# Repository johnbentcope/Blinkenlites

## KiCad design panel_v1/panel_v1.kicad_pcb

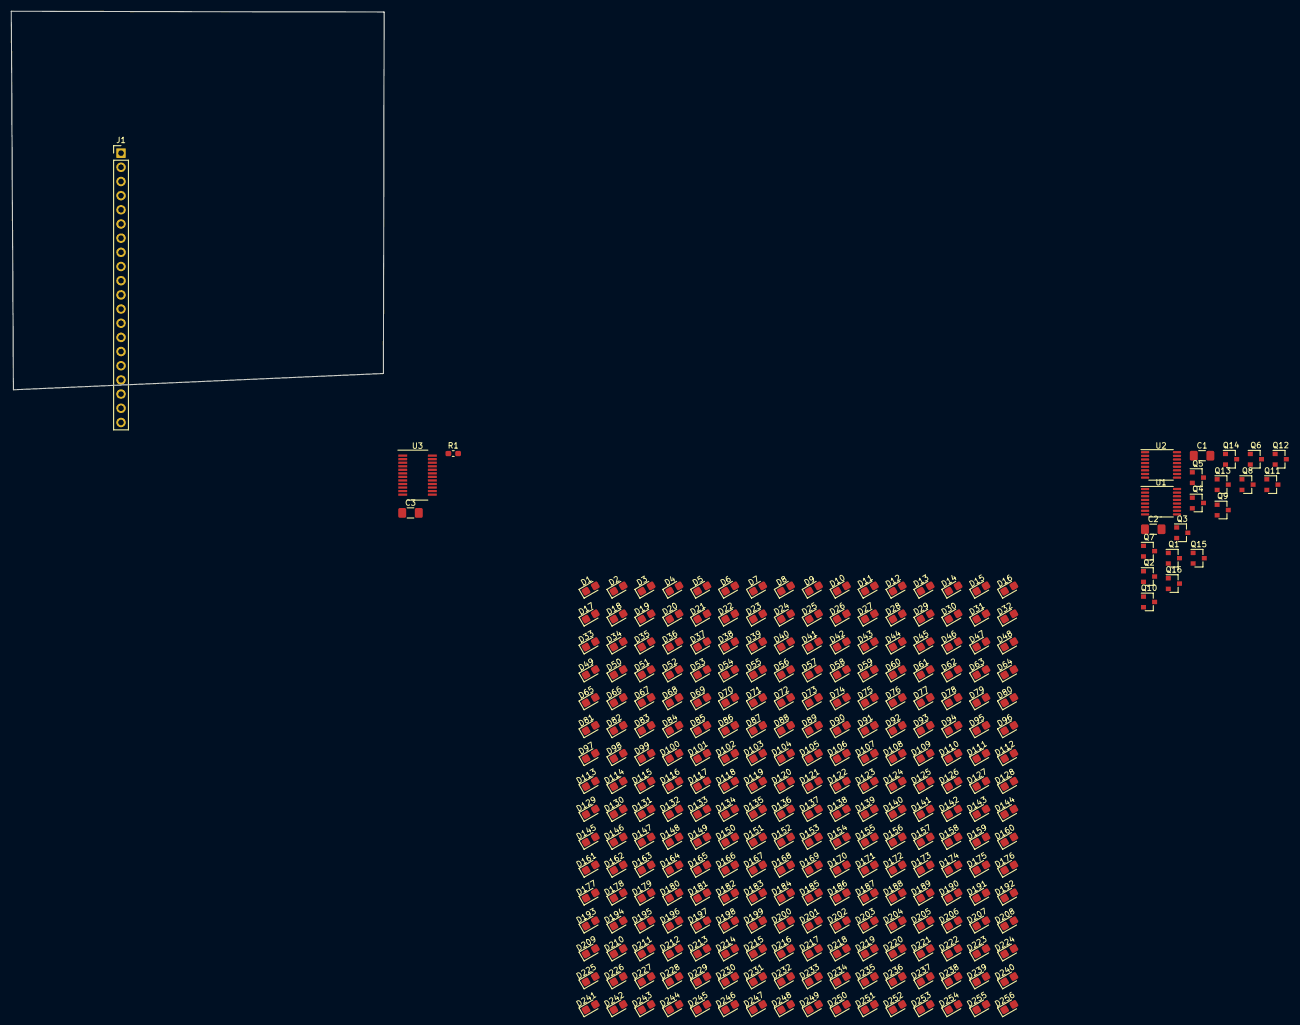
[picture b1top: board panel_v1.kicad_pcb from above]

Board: 2 copper layers, 66.8 x 67.8 mm, 280 parts (0 on the bottom side), 59 nets, no tracks yet.

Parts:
C1, C2, C3: 100nF; C_1206_3216Metric_Pad1.42x1.75mm_HandSolder
D1, D2, D3, D4, D5, D6, D7, D8, D9, D10, D11, D12, D13, D14, D15, D16, D17, D18, D19, D20, D21, D22, D23, D24, D25, D26, D27, D28, D29, D30, D31, D32, D33, D34, D35, D36, D37, D38, D39, D40, D41, D42, D43, D44, D45, D46, D47, D48, D49, D50, D51, D52, D53, D54, D55, D56, D57, D58, D59, D60, D61, D62, D63, D64, D65, D66, D67, D68, D69, D70, D71, D72, D73, D74, D75, D76, D77, D78, D79, D80, D81, D82, D83, D84, D85, D86, D87, D88, D89, D90, D91, D92, D93, D94, D95, D96, D97, D98, D99, D100, D101, D102, D103, D104, D105, D106, D107, D108, D109, D110, D111, D112, D113, D114, D115, D116, D117, D118, D119, D120, D121, D122, D123, D124, D125, D126, D127, D128, D129, D130, D131, D132, D133, D134, D135, D136, D137, D138, D139, D140, D141, D142, D143, D144, D145, D146, D147, D148, D149, D150, D151, D152, D153, D154, D155, D156, D157, D158, D159, D160, D161, D162, D163, D164, D165, D166, D167, D168, D169, D170, D171, D172, D173, D174, D175, D176, D177, D178, D179, D180, D181, D182, D183, D184, D185, D186, D187, D188, D189, D190, D191, D192, D193, D194, D195, D196, D197, D198, D199, D200, D201, D202, D203, D204, D205, D206, D207, D208, D209, D210, D211, D212, D213, D214, D215, D216, D217, D218, D219, D220, D221, D222, D223, D224, D225, D226, D227, D228, D229, D230, D231, D232, D233, D234, D235, D236, D237, D238, D239, D240, D241, D242, D243, D244, D245, D246, D247, D248, D249, D250, D251, D252, D253, D254, D255, D256: LED; LED_0805_2012Metric_Castellated
J1: Conn_01x20; PinHeader_1x20_P2.54mm_Vertical
Q1, Q2, Q3, Q4, Q5, Q6, Q7, Q8, Q9, Q10, Q11, Q12, Q13, Q14, Q15, Q16: AO3401A; SOT-23
R1: R; R_0603_1608Metric_Pad1.05x0.95mm_HandSolder
U1, U2: 74HC595; TSSOP-16_4.4x5mm_P0.65mm
U3: TLC59025; QSOP-24_3.9x8.7mm_P0.635mm

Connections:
/AMBER: J1.6, U3.2 (SDI)
/BLANK: J1.12, U3.21 (~OE)
/LATCH: J1.11, U3.4 (LE)
/ROWblank: J1.16, U1.13 (~OE), U2.13 (~OE)
/ROWdat: J1.14, U1.14 (SER)
/ROWlatch: J1.15, U1.12 (RCLK), U2.12 (RCLK)
/SCLK: J1.10, U1.11 (SRCLK), U2.11 (SRCLK), U3.3 (CLK)
/ledArray/COM: D97.2 (A), D98.2 (A), D99.2 (A), D100.2 (A), D101.2 (A), D102.2 (A), D103.2 (A), D104.2 (A), D105.2 (A), D106.2 (A), D107.2 (A), D108.2 (A), D109.2 (A), D110.2 (A), D111.2 (A), D112.2 (A), Q7.3 (D)
/ledArray/COM_1: D225.2 (A), D226.2 (A), D227.2 (A), D228.2 (A), D229.2 (A), D230.2 (A), D231.2 (A), D232.2 (A), D233.2 (A), D234.2 (A), D235.2 (A), D236.2 (A), D237.2 (A), D238.2 (A), D239.2 (A), D240.2 (A), Q15.3 (D)
/ledArray/COM_2: D177.2 (A), D178.2 (A), D179.2 (A), D180.2 (A), D181.2 (A), D182.2 (A), D183.2 (A), D184.2 (A), D185.2 (A), D186.2 (A), D187.2 (A), D188.2 (A), D189.2 (A), D190.2 (A), D191.2 (A), D192.2 (A), Q12.3 (D)
/ledArray/COM_3: D161.2 (A), D162.2 (A), D163.2 (A), D164.2 (A), D165.2 (A), D166.2 (A), D167.2 (A), D168.2 (A), D169.2 (A), D170.2 (A), D171.2 (A), D172.2 (A), D173.2 (A), D174.2 (A), D175.2 (A), D176.2 (A), Q11.3 (D)
/ledArray/COM_4: D129.2 (A), D130.2 (A), D131.2 (A), D132.2 (A), D133.2 (A), D134.2 (A), D135.2 (A), D136.2 (A), D137.2 (A), D138.2 (A), D139.2 (A), D140.2 (A), D141.2 (A), D142.2 (A), D143.2 (A), D144.2 (A), Q9.3 (D)
/ledArray/COM_5: D193.2 (A), D194.2 (A), D195.2 (A), D196.2 (A), D197.2 (A), D198.2 (A), D199.2 (A), D200.2 (A), D201.2 (A), D202.2 (A), D203.2 (A), D204.2 (A), D205.2 (A), D206.2 (A), D207.2 (A), D208.2 (A), Q13.3 (D)
/ledArray/COM_6: D209.2 (A), D210.2 (A), D211.2 (A), D212.2 (A), D213.2 (A), D214.2 (A), D215.2 (A), D216.2 (A), D217.2 (A), D218.2 (A), D219.2 (A), D220.2 (A), D221.2 (A), D222.2 (A), D223.2 (A), D224.2 (A), Q14.3 (D)
/ledArray/COM_7: D241.2 (A), D242.2 (A), D243.2 (A), D244.2 (A), D245.2 (A), D246.2 (A), D247.2 (A), D248.2 (A), D249.2 (A), D250.2 (A), D251.2 (A), D252.2 (A), D253.2 (A), D254.2 (A), D255.2 (A), D256.2 (A), Q16.3 (D)
/ledArray/COM_8: D145.2 (A), D146.2 (A), D147.2 (A), D148.2 (A), D149.2 (A), D150.2 (A), D151.2 (A), D152.2 (A), D153.2 (A), D154.2 (A), D155.2 (A), D156.2 (A), D157.2 (A), D158.2 (A), D159.2 (A), D160.2 (A), Q10.3 (D)
/ledArray/COM_9: D81.2 (A), D82.2 (A), D83.2 (A), D84.2 (A), D85.2 (A), D86.2 (A), D87.2 (A), D88.2 (A), D89.2 (A), D90.2 (A), D91.2 (A), D92.2 (A), D93.2 (A), D94.2 (A), D95.2 (A), D96.2 (A), Q6.3 (D)
/ledArray/COM_10: D49.2 (A), D50.2 (A), D51.2 (A), D52.2 (A), D53.2 (A), D54.2 (A), D55.2 (A), D56.2 (A), D57.2 (A), D58.2 (A), D59.2 (A), D60.2 (A), D61.2 (A), D62.2 (A), D63.2 (A), D64.2 (A), Q4.3 (D)
/ledArray/COM_11: D33.2 (A), D34.2 (A), D35.2 (A), D36.2 (A), D37.2 (A), D38.2 (A), D39.2 (A), D40.2 (A), D41.2 (A), D42.2 (A), D43.2 (A), D44.2 (A), D45.2 (A), D46.2 (A), D47.2 (A), D48.2 (A), Q3.3 (D)
/ledArray/COM_12: D17.2 (A), D18.2 (A), D19.2 (A), D20.2 (A), D21.2 (A), D22.2 (A), D23.2 (A), D24.2 (A), D25.2 (A), D26.2 (A), D27.2 (A), D28.2 (A), D29.2 (A), D30.2 (A), D31.2 (A), D32.2 (A), Q2.3 (D)
/ledArray/COM_13: D65.2 (A), D66.2 (A), D67.2 (A), D68.2 (A), D69.2 (A), D70.2 (A), D71.2 (A), D72.2 (A), D73.2 (A), D74.2 (A), D75.2 (A), D76.2 (A), D77.2 (A), D78.2 (A), D79.2 (A), D80.2 (A), Q5.3 (D)
/ledArray/COM_14: D1.2 (A), D2.2 (A), D3.2 (A), D4.2 (A), D5.2 (A), D6.2 (A), D7.2 (A), D8.2 (A), D9.2 (A), D10.2 (A), D11.2 (A), D12.2 (A), D13.2 (A), D14.2 (A), D15.2 (A), D16.2 (A), Q1.3 (D)
/ledArray/COM_15: D113.2 (A), D114.2 (A), D115.2 (A), D116.2 (A), D117.2 (A), D118.2 (A), D119.2 (A), D120.2 (A), D121.2 (A), D122.2 (A), D123.2 (A), D124.2 (A), D125.2 (A), D126.2 (A), D127.2 (A), D128.2 (A), Q8.3 (D)
COL_0: D1.1 (K), D17.1 (K), D33.1 (K), D49.1 (K), D65.1 (K), D81.1 (K), D97.1 (K), D113.1 (K), D129.1 (K), D145.1 (K), D161.1 (K), D177.1 (K), D193.1 (K), D209.1 (K), D225.1 (K), D241.1 (K), U3.5 (OUT0)
COL_1: D2.1 (K), D18.1 (K), D34.1 (K), D50.1 (K), D66.1 (K), D82.1 (K), D98.1 (K), D114.1 (K), D130.1 (K), D146.1 (K), D162.1 (K), D178.1 (K), D194.1 (K), D210.1 (K), D226.1 (K), D242.1 (K), U3.6 (OUT1)
COL_2: D3.1 (K), D19.1 (K), D35.1 (K), D51.1 (K), D67.1 (K), D83.1 (K), D99.1 (K), D115.1 (K), D131.1 (K), D147.1 (K), D163.1 (K), D179.1 (K), D195.1 (K), D211.1 (K), D227.1 (K), D243.1 (K), U3.7 (OUT2)
COL_3: D4.1 (K), D20.1 (K), D36.1 (K), D52.1 (K), D68.1 (K), D84.1 (K), D100.1 (K), D116.1 (K), D132.1 (K), D148.1 (K), D164.1 (K), D180.1 (K), D196.1 (K), D212.1 (K), D228.1 (K), D244.1 (K), U3.8 (OUT3)
COL_4: D5.1 (K), D21.1 (K), D37.1 (K), D53.1 (K), D69.1 (K), D85.1 (K), D101.1 (K), D117.1 (K), D133.1 (K), D149.1 (K), D165.1 (K), D181.1 (K), D197.1 (K), D213.1 (K), D229.1 (K), D245.1 (K), U3.9 (OUT4)
COL_5: D6.1 (K), D22.1 (K), D38.1 (K), D54.1 (K), D70.1 (K), D86.1 (K), D102.1 (K), D118.1 (K), D134.1 (K), D150.1 (K), D166.1 (K), D182.1 (K), D198.1 (K), D214.1 (K), D230.1 (K), D246.1 (K), U3.10 (OUT5)
COL_6: D7.1 (K), D23.1 (K), D39.1 (K), D55.1 (K), D71.1 (K), D87.1 (K), D103.1 (K), D119.1 (K), D135.1 (K), D151.1 (K), D167.1 (K), D183.1 (K), D199.1 (K), D215.1 (K), D231.1 (K), D247.1 (K), U3.11 (OUT6)
COL_7: D8.1 (K), D24.1 (K), D40.1 (K), D56.1 (K), D72.1 (K), D88.1 (K), D104.1 (K), D120.1 (K), D136.1 (K), D152.1 (K), D168.1 (K), D184.1 (K), D200.1 (K), D216.1 (K), D232.1 (K), D248.1 (K), U3.12 (OUT7)
COL_8: D9.1 (K), D25.1 (K), D41.1 (K), D57.1 (K), D73.1 (K), D89.1 (K), D105.1 (K), D121.1 (K), D137.1 (K), D153.1 (K), D169.1 (K), D185.1 (K), D201.1 (K), D217.1 (K), D233.1 (K), D249.1 (K), U3.13 (OUT8)
COL_9: D10.1 (K), D26.1 (K), D42.1 (K), D58.1 (K), D74.1 (K), D90.1 (K), D106.1 (K), D122.1 (K), D138.1 (K), D154.1 (K), D170.1 (K), D186.1 (K), D202.1 (K), D218.1 (K), D234.1 (K), D250.1 (K), U3.14 (OUT9)
COL_10: D11.1 (K), D27.1 (K), D43.1 (K), D59.1 (K), D75.1 (K), D91.1 (K), D107.1 (K), D123.1 (K), D139.1 (K), D155.1 (K), D171.1 (K), D187.1 (K), D203.1 (K), D219.1 (K), D235.1 (K), D251.1 (K), U3.15 (OUT10)
COL_11: D12.1 (K), D28.1 (K), D44.1 (K), D60.1 (K), D76.1 (K), D92.1 (K), D108.1 (K), D124.1 (K), D140.1 (K), D156.1 (K), D172.1 (K), D188.1 (K), D204.1 (K), D220.1 (K), D236.1 (K), D252.1 (K), U3.16 (OUT11)
COL_12: D13.1 (K), D29.1 (K), D45.1 (K), D61.1 (K), D77.1 (K), D93.1 (K), D109.1 (K), D125.1 (K), D141.1 (K), D157.1 (K), D173.1 (K), D189.1 (K), D205.1 (K), D221.1 (K), D237.1 (K), D253.1 (K), U3.17 (OUT12)
COL_13: D14.1 (K), D30.1 (K), D46.1 (K), D62.1 (K), D78.1 (K), D94.1 (K), D110.1 (K), D126.1 (K), D142.1 (K), D158.1 (K), D174.1 (K), D190.1 (K), D206.1 (K), D222.1 (K), D238.1 (K), D254.1 (K), U3.18 (OUT13)
COL_14: D15.1 (K), D31.1 (K), D47.1 (K), D63.1 (K), D79.1 (K), D95.1 (K), D111.1 (K), D127.1 (K), D143.1 (K), D159.1 (K), D175.1 (K), D191.1 (K), D207.1 (K), D223.1 (K), D239.1 (K), D255.1 (K), U3.19 (OUT14)
COL_15: D16.1 (K), D32.1 (K), D48.1 (K), D64.1 (K), D80.1 (K), D96.1 (K), D112.1 (K), D128.1 (K), D144.1 (K), D160.1 (K), D176.1 (K), D192.1 (K), D208.1 (K), D224.1 (K), D240.1 (K), D256.1 (K), U3.20 (OUT15)
GND: C1.1, C2.1, C3.1, J1.1, J1.2, J1.9, J1.13, J1.17, R1.2, U1.8 (GND), U3.1 (GND)
unnamed: Q1.1 (G), U1.15 (QA)
unnamed: Q2.1 (G), U1.1 (QB)
unnamed: Q3.1 (G), U1.2 (QC)
unnamed: Q4.1 (G), U1.3 (QD)
unnamed: Q5.1 (G), U1.4 (QE)
unnamed: Q6.1 (G), U1.5 (QF)
unnamed: Q7.1 (G), U1.6 (QG)
unnamed: Q8.1 (G), U1.7 (QH)
unnamed: Q9.1 (G), U2.15 (QA)
unnamed: Q10.1 (G), U2.1 (QB)
unnamed: Q11.1 (G), U2.2 (QC)
unnamed: Q12.1 (G), U2.3 (QD)
unnamed: Q13.1 (G), U2.4 (QE)
unnamed: Q14.1 (G), U2.5 (QF)
unnamed: Q15.1 (G), U2.6 (QG)
unnamed: Q16.1 (G), U2.7 (QH)
unnamed: R1.1, U3.23 (R-EXT)
unnamed: U1.9 (QH'), U2.14 (SER)
P_LED: C1.2, C2.2, C3.2, J1.3, J1.4, J1.5, J1.18, J1.19, J1.20, Q1.2 (S), Q2.2 (S), Q3.2 (S), Q4.2 (S), Q5.2 (S), Q6.2 (S), Q7.2 (S), Q8.2 (S), Q9.2 (S), Q10.2 (S), Q11.2 (S), Q12.2 (S), Q13.2 (S), Q14.2 (S), Q15.2 (S), Q16.2 (S), U1.10 (~SRCLR), U1.16 (VCC), U2.10 (~SRCLR), U2.16 (VCC), U3.24 (VDD)

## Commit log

2020-05-24 getting started
2020-06-21 starting work on monochrome screen
2020-06-21 starting work on rgb screen
2020-07-31 blinkenlites
2020-07-31 updating schematic
2021-01-23 added PixelPurse reverse engineered schematic
2021-01-23 Added README
2021-01-26 testing
